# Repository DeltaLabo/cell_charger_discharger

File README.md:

Electrochemical Cell Charger/Discharger/Tester -- README {#mainpage}
============

### Most recent version of this repository can be found in: ###

* [Bitbucket](https://bitbucket.org/juanjorojash/cell_charger_discharger/src/master/)

### Documentation ###

* Full documentation in HTLM version can be found in **[repository directory]/documentation/htlm/index.htlm**

### What is this repository for? ###

* This repository was created to be used in conjuction with the integrated system known as "Charger_discharger.V5". The latest . It was created to control the PIC16F1786 installed for feedback control and serial logging.
* Hardware version: Charger_discharger.V5
* PCB design files  located in **[repository directory]/pcb/**

### How do I get set up? ###

* Connect usign serial cable model "TTL-232R-5V-AJ". 
* **Serial terminal** Start with the following settings BR:57600 kbps, Data: 8 bit, Parity: none, Stop bits: 1, Flow control: none. Press "ESC" to restart and show the main menu. Set the desired configuration following the instructions.
* **LabView logger program** A program for receiving, saving and plotting the test data is included in the repository, in the directory **labview_logger/logger.exe**. The following programs are needed in order to run this program in a PC that **does not** have LabView installed:
	* [LabVIEW Run-Time Engine 2016 - (64-bit)](http://www.ni.com/download/labview-run-time-engine-2016/6067/en/) 
	* [NI-VISA Run-Time Engine 16.0](http://www.ni.com/download/ni-visa-run-time-engine-16.0/6188/en/)
The program creates the directory **c:/logger_data** to store the data.

### Contribution guidelines ###

* If you want to propose a review or need to modify the code for any reason first clone this [repository](https://bitbucket.org/juanjorojash/cell_charger_discharger/src/master/) in your PC and create a new branch for your changes. Once your changes are complete and fully tested ask the administrator permission to push this new branch into the source.
* If you just want to do local changes instead you can download a zip version of the repository and do all changes locally in your PC. 

### Who do I talk to? ###

* [Juan J. Rojas](mailto:juan.rojas@itcr.ac.cr)

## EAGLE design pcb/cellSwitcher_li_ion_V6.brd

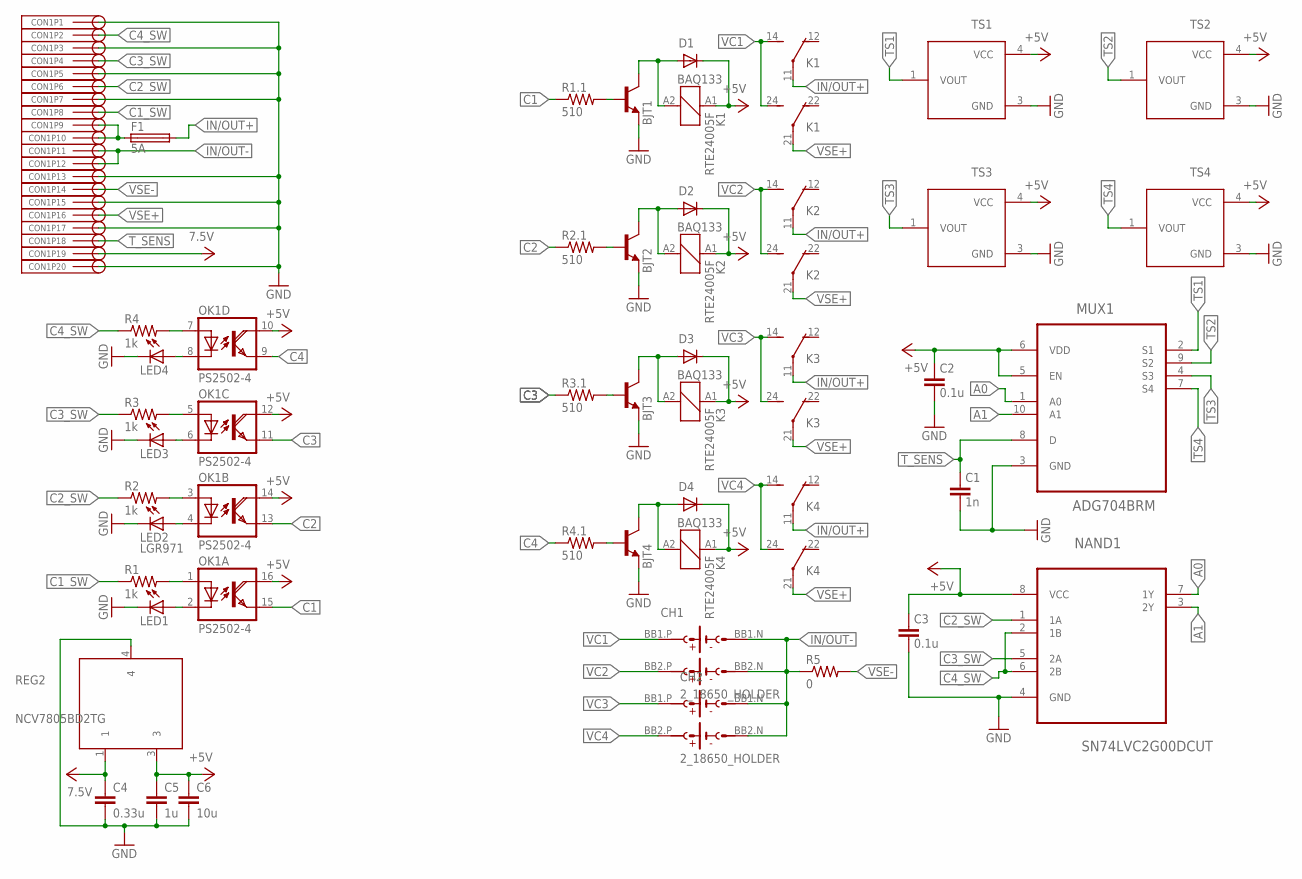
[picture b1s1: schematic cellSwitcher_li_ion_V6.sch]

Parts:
BJT1, BJT2, BJT3, BJT4: BC818K-40; SOT-23
C1: 1n; C0603
C2, C3: 0.1u; C0603
C4: 0.33u; C0603
C5: 1u; C0603
C6: 10u; C0603
CH1, CH2: 2_18650_HOLDER
CON1: TMM-110-01-F-D-RA
D1, D2, D3, D4: BAQ133; SOD08
F1: 5A; SH22,5
K1, K2, K3, K4: RTE24005F
LED1, LED2, LED3, LED4: LGR971; SML0805
MUX1: ADG704BRM; MSOP10
NAND1: SN74LVC2G00DCUT; VSSOP-8
OK1: PS2502-4; DIL16
R1, R2, R3, R4: 1k; R0603
R1.1, R2.1, R3.1, R4.1: 510; R0603
R5: 0; R0603
REG2: NCV7805BD2TG; D2PAK-3
TS1, TS2, TS3, TS4: STLM20DD9F; UDFN-4L

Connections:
7.5V: C4.1, CON1.19, REG2.1
+5V: C2.1, C3.1, C5.1, C6.1, D1.C, D2.C, D3.C, D4.C, K1.A1 (1), K2.A1 (1), K3.A1 (1), K4.A1 (1), MUX1.5 (EN), MUX1.6 (VDD), NAND1.8 (VCC), OK1.10 (COL), OK1.12 (COL), OK1.14 (COL), OK1.16 (COL), REG2.3, TS1.4 (VCC), TS2.4 (VCC), TS3.4 (VCC), TS4.4 (VCC)
A0: MUX1.1 (A0), NAND1.7 (1Y)
A1: MUX1.10 (A1), NAND1.3 (2Y)
C1: OK1.15 (EMI), R1.1.1
C1_SW: CON1.8, R1.1
C2: OK1.13 (EMI), R2.1.1
C2_SW: CON1.6, NAND1.1 (1A), R2.1
C3: OK1.11 (EMI), R3.1.1
C3_SW: CON1.4, NAND1.5 (2A), R3.1
C4: OK1.9 (EMI), R4.1.1
C4_SW: CON1.2, NAND1.2 (1B), NAND1.6 (2B), R4.1
GND: BJT1.2 (E), BJT2.2 (E), BJT3.2 (E), BJT4.2 (E), C1.2, C2.2, C3.2, C4.2, C5.2, C6.2, CON1.1, CON1.3, CON1.5, CON1.7, CON1.13, CON1.15, CON1.17, CON1.20, LED1.C, LED2.C, LED3.C, LED4.C, MUX1.3 (GND), NAND1.4 (GND), REG2.4, TS1.3 (GND), TS2.3 (GND), TS3.3 (GND), TS4.3 (GND)
IN/OUT+: F1.2, K1.11 (COM), K2.11 (COM), K3.11 (COM), K4.11 (COM)
IN/OUT+1: CON1.9, CON1.10, F1.1
IN/OUT-: CH1.BB1.N (B1.N), CH1.BB2.N (B2.N), CH2.BB1.N (B1.N), CH2.BB2.N (B2.N), CON1.11, CON1.12, R5.1
unnamed: BJT1.1 (B), R1.1.2
unnamed: BJT2.1 (B), R2.1.2
unnamed: BJT3.1 (B), R3.1.2
unnamed: BJT3.3 (C), D3.A, K3.A2 (2)
unnamed: LED1.A, OK1.2 (C)
unnamed: LED2.A, OK1.4 (C)
unnamed: LED3.A, OK1.6 (C)
unnamed: LED4.A, OK1.8 (C)
unnamed: OK1.7 (A), R4.2
unnamed: OK1.5 (A), R3.2
unnamed: OK1.3 (A), R2.2
unnamed: OK1.1 (A), R1.2
unnamed: BJT1.3 (C), D1.A, K1.A2 (2)
unnamed: BJT2.3 (C), D2.A, K2.A2 (2)
unnamed: BJT4.1 (B), R4.1.2
unnamed: BJT4.3 (C), D4.A, K4.A2 (2)
TS1: MUX1.2 (S1), TS1.1 (VOUT)
TS2: MUX1.9 (S2), TS2.1 (VOUT)
TS3: MUX1.4 (S3), TS3.1 (VOUT)
TS4: MUX1.7 (S4), TS4.1 (VOUT)
T_SENS: C1.1, CON1.18, MUX1.8 (D)
VC1: CH1.BB1.P (B1.P), K1.14 (NO), K1.24 (NO)
VC2: CH1.BB2.P (B2.P), K2.14 (NO), K2.24 (NO)
VC3: CH2.BB1.P (B1.P), K3.14 (NO), K3.24 (NO)
VC4: CH2.BB2.P (B2.P), K4.14 (NO), K4.24 (NO)
VSE+: CON1.16, K1.21 (COM), K2.21 (COM), K3.21 (COM), K4.21 (COM)
VSE-: CON1.14, R5.2

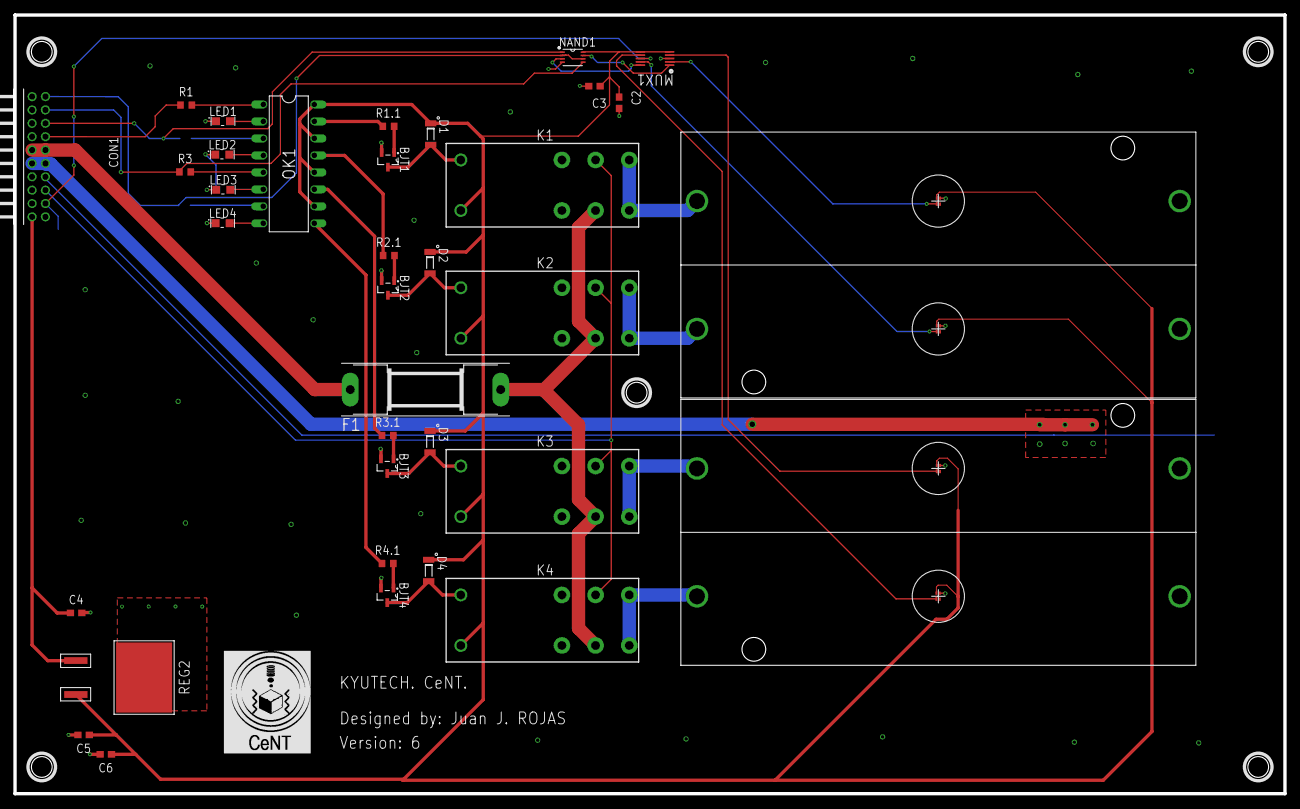
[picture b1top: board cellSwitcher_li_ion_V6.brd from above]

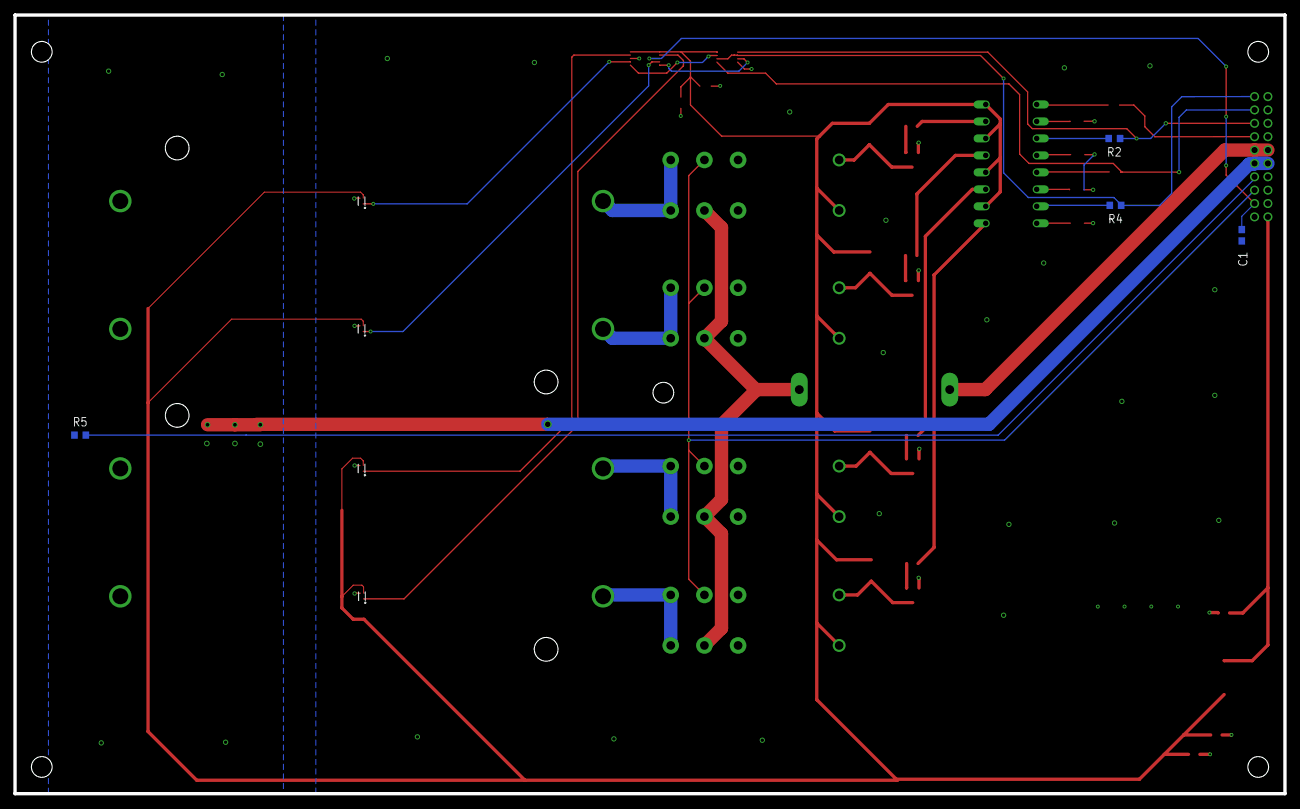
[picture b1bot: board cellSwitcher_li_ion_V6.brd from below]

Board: 2 copper layers, 190.0 x 116.5 mm, 43 parts (4 on the bottom side), 43 nets.

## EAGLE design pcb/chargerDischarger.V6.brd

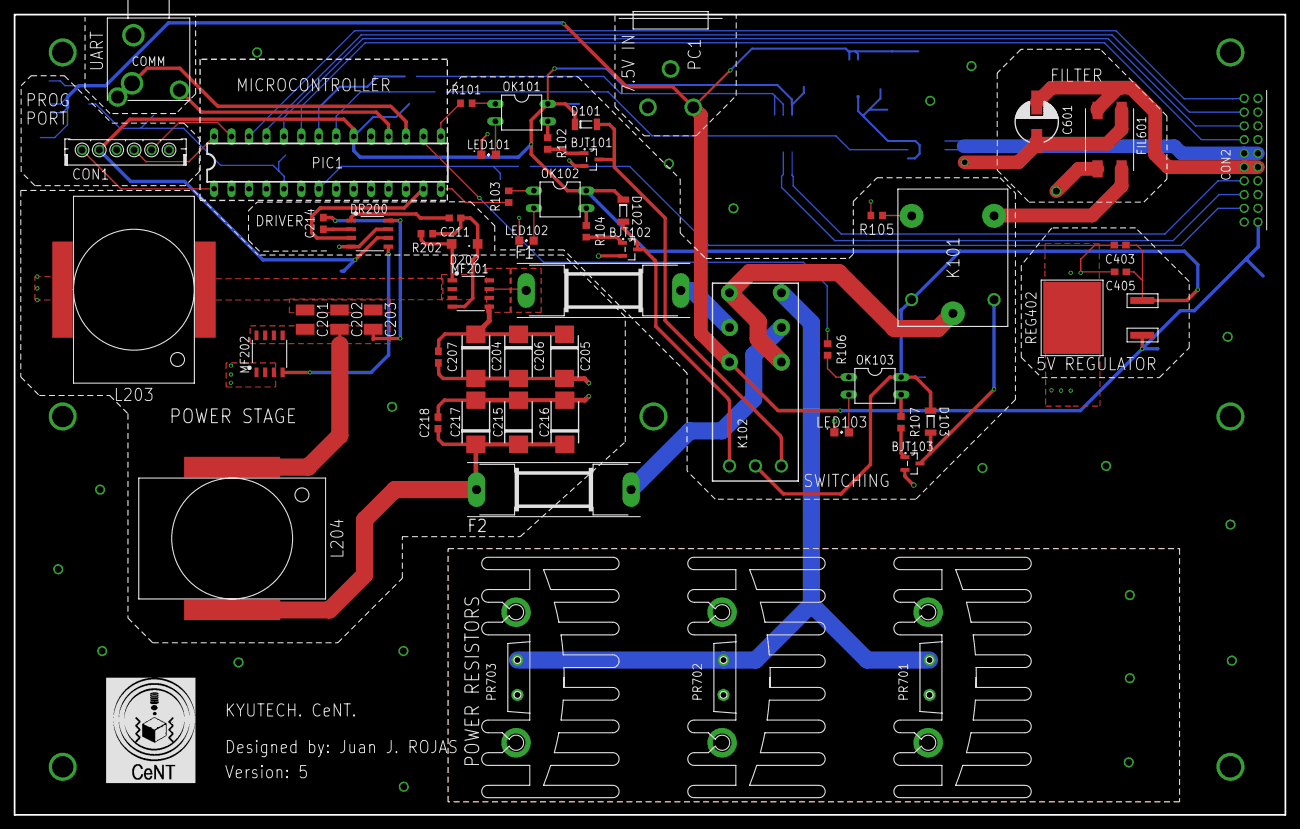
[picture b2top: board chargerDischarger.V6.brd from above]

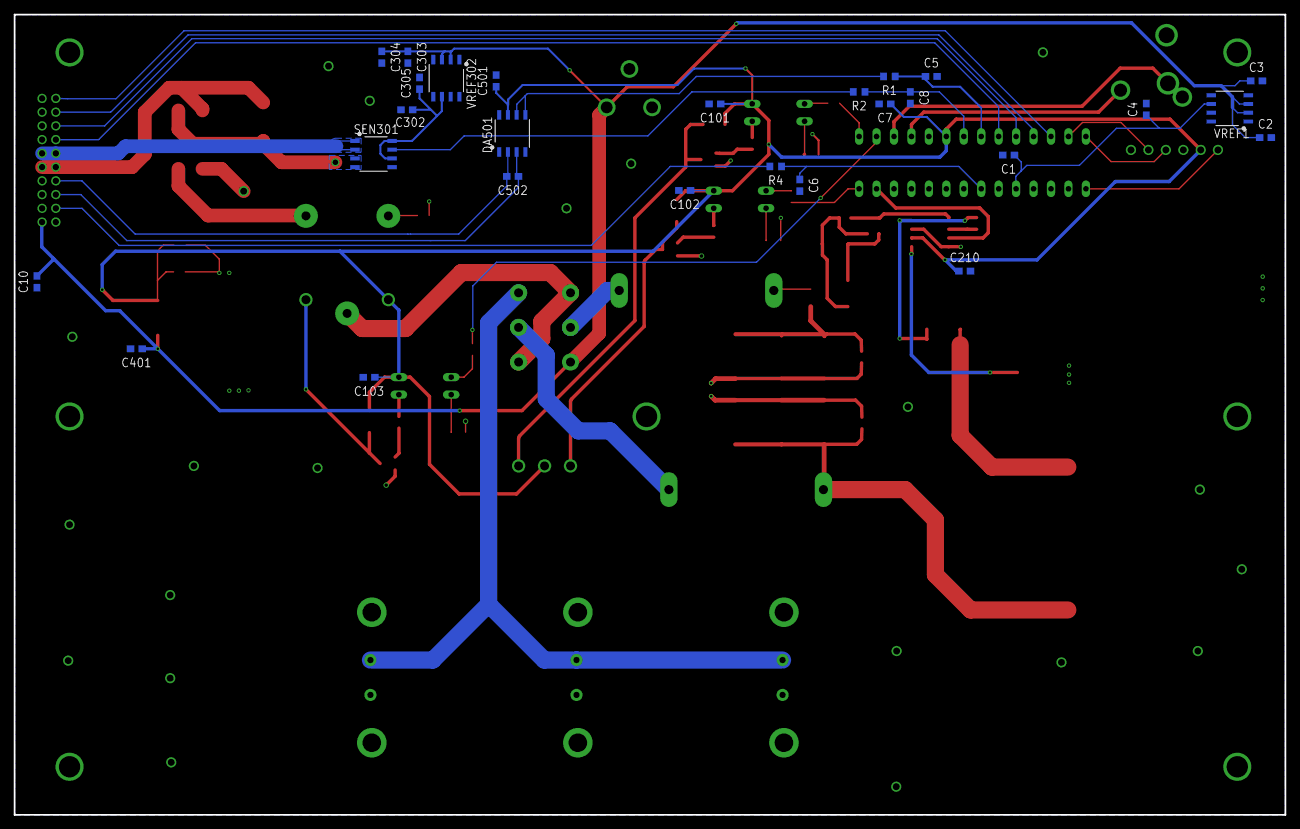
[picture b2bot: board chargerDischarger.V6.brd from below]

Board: 2 copper layers, 185.0 x 116.5 mm, 83 parts (27 on the bottom side), 58 nets.

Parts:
BJT101, BJT102, BJT103: BC818K-40; SOT-23
C1, C3, C6, C7, C101, C102, C103, C210, C214, C302, C304, C403: 1u; C0603
C2, C10, C303, C405: 10u; C0603
C4, C207, C218, C305, C501: 0.1u; C0603
C5, C8, C502: 1n; C0603
C201, C202, C203: 10u; C1210
C204, C205, C206, C215, C216, C217: 33u_Tan; C7343
C211: 10n; C0603
C401: 0.33u; C0603
C601: 100u; D6.3_AEC
COMM: AUDIO_JACK-3.5MM; KLBR4
CON1: B6B-EH-A
CON2: SQT-110-01-F-D-RA
D101, D102, D103: BAQ133; SOD08
D202: SOD123
DA501: MAX4198; SOIC-8
DR200: MCP14628-E/SN; SOIC-8
F1, F2: 4A; SH22,5
FIL601: ACM9070-701
K101: ORWH; ORWH-SS-105D1F
K102: RT424F05054; RT424F05
L203, L204: 68µ; 60B683C
LED101, LED102, LED103: LGR971; SML0805
MF201, MF202: SI4154DY; SOIC-8
OK101, OK102, OK103: PS2502-1; DIL04
PC1: 722RA
PIC1: PIC16F1786-SPDIP; SPDIP-28
PR701, PR702, PR703: 1; TO-220HEATSINK
R1, R2: 0; R0603
R4: 200; R0603
R101, R103, R106, R202: 1k; R0603
R102, R104, R107: 510; R0603
R105: 10M; R0603
REG402: NCV7805BD2TG; D2PAK-3
SEN301: ACS723-05AB-T; SOIC-8
VREF1, VREF302: REF195GSZ; SOIC-8

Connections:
7.5V: C2.1, C3.1, C10.2, C303.1, C304.1, C401.1, CON2.19, K102.22, PC1.PIN, REG402.1, VREF1.2, VREF1.3, VREF302.2, VREF302.3
+5V: C7.1, C101.1, C102.1, C103.1, C210.1, C403.1, C405.1, C501.1, CON1.2, D101.C, D102.C, D103.C, DA501.7, DR200.6, K101.B1, K102.A3, OK101.4, OK102.4, OK103.4, PIC1.20, REG402.3
BI_CURR_MEAS1:N$1: C302.1, C305.1, SEN301.6, SEN301.8, VREF302.6
C1_SW: CON2.8, PIC1.23
C2_SW: CON2.6, PIC1.24
C3_SW: CON2.4, PIC1.25
C4_SW: CON2.2, PIC1.26
CHAR: PIC1.15, R101.1
DISC: PIC1.14, R103.1
GND: BJT101.2, BJT102.2, BJT103.2, C1.2, C2.2, C3.2, C4.2, C5.2, C6.2, C7.2, C8.2, C10.1, C101.2, C102.2, C103.2, C204.-, C205.-, C206.-, C207.2, C210.2, C215.-, C216.-, C217.-, C218.2, C302.2, C303.2, C304.2, C305.2, C401.2, C403.2, C405.2, C501.2, COMM.S, CON1.3, CON2.1, CON2.3, CON2.5, CON2.7, CON2.13, CON2.15, CON2.17, CON2.20, DA501.1, DA501.4, DR200.4, DR200.7, FIL601.P$3, L203.2, LED101.C, LED102.C, LED103.C, MF202.1, MF202.2, MF202.3, PC1.SLEEVE, PC1.SLEEVE_SHUNT, PIC1.8, PIC1.19, PR701.D1, PR701.D2, PR701.R1, PR702.D1, PR702.D2, PR702.R1, PR703.D1, PR703.D2, PR703.R1, R105.2, REG402.4, SEN301.5, VREF1.4, VREF302.4
ICSPCLK: CON1.5, PIC1.27
ICSPDAT: CON1.4, PIC1.28
IN/OUT+: CON2.9, CON2.10, SEN301.1, SEN301.2
IN/OUT-: C601.NEG, CON2.11, CON2.12, FIL601.P$2
I_SENS: R2.2, SEN301.7
MCLR: CON1.1, PIC1.1
unnamed: C8.1, PIC1.21, R2.1
unnamed: C5.1, PIC1.22, R1.1
unnamed: C6.1, PIC1.7, R4.1
unnamed: C1.1, C4.1, PIC1.5, VREF1.6
unnamed: C601.POS, FIL601.P$1, SEN301.3, SEN301.4
unnamed: FIL601.P$4, K101.NO
unnamed: F1.2, K102.21
unnamed: F2.2, K102.11
ON/OFF: PIC1.16, R106.1
POWER_RESISTOR: K102.14, PR701.R2, PR702.R2, PR703.R2
PWM: DR200.3, PIC1.13
RX: COMM.B, COMM.R, PIC1.17
SWITCH1:N$1: BJT101.1, R102.2
SWITCH1:N$2: BJT101.3, D101.A, K102.A1
SWITCH1:N$3: LED102.A, OK102.2
SWITCH1:N$4: OK102.1, R103.2
SWITCH1:N$5: OK102.3, R104.1
SWITCH1:N$6: BJT102.1, R104.2
SWITCH1:N$7: BJT102.3, D102.A, K102.A2
SWITCH1:N$8: K101.NC, R105.1
SWITCH1:N$9: LED103.A, OK103.2
SWITCH1:N$10: OK103.1, R106.2
SWITCH1:N$11: LED101.A, OK101.2
SWITCH1:N$12: OK101.1, R101.2
SWITCH1:N$13: OK101.3, R102.1
SWITCH1:N$14: OK103.3, R107.1
SWITCH1:N$15: BJT103.1, R107.2
SWITCH1:N$16: BJT103.3, D103.A, K101.B2
SWITCH1:TEST: K101.COM, K102.12, K102.24
TX: COMM.T, PIC1.18
T_SENS: CON2.18, R4.2
VSE+: C502.1, CON2.16, DA501.3
VSE-: C502.2, CON2.14, DA501.2
V_SENS: DA501.5, DA501.6, R1.2
ZETA_CONV1:L1_IN1: C201.1, C202.1, C203.1, D202.A, L203.1, MF201.1, MF201.2, MF201.3, R202.2
ZETA_CONV1:L2_IN1: C201.2, C202.2, C203.2, C214.2, DR200.8, L204.1, MF202.5, MF202.6, MF202.7, MF202.8
ZETA_CONV1:N$10: DR200.5, MF202.4
ZETA_CONV1:N$28: C214.1, DR200.2
ZETA_CONV1:N$29: C211.2, DR200.1
ZETA_CONV1:N$30: C211.1, D202.C, MF201.4, R202.1
ZETA_IN: C204.+, C205.+, C206.+, C207.1, F1.1, MF201.5, MF201.6, MF201.7, MF201.8
ZETA_OUT: C215.+, C216.+, C217.+, C218.1, F2.1, L204.2

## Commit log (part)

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2018-07-05 First commit. Configuration bit changed
2018-07-10 Timer0 is working. Some code was included in the main to test that it can count 1 second. WDT needs to be deactivated in order to make this work because they share the same prescaler.
2018-07-10 PWM of 8 bits is ready, out of the oven. Only an 8 bit register to set the DC, from 0 to 100 without change of resolution. The price to pay was changing frequency to 250kHz.
2018-07-10 ADC is working, ready FI BUM DEM. However, the ouput is a little crazy
2018-07-12 Now the measurements of the ADC are correct, the control loop is now at 1kHz. I'm about to make changes to the PID stuff.
2018-07-12 First attemp to make it work in the real stuff.
2018-07-13 Ready for test in the computer usign LabView. Tunning of the controller is not finish and change to switch case is requiered too
2018-07-17 Tested with Labview, test at 200Khz create some sound problems
2018-07-17 Test at 500Khz, same proplem
2018-07-17 125Khz test working, just need to tune everything
2018-07-17 Tune of PI in coarse way, let's see how it reacts
2018-07-17 At 125Khz everything works fine, however incorporating the Differential part of the controller seems now a good idea. I could really improve the CV part.
2018-07-19 Many changes, see if I can make it work
2018-07-20 A problem with the transition between CC and CV, I will solve it. The rest is better than anytime before
2018-08-01 Some incremental stepping in the ki when CV is reached. Also right now is running with FCCM of the mosfet driving chip activated.
2018-08-01 This is the real working point!!
2018-08-01 Very good behaviour at low current. Incremental of the duty cycle can be a good idea.
2018-08-03 Some changes to the way it logs in TESTBENCH
2018-08-03 Implemented STANDBY and IDLE state
2018-08-03 CHARGE DISCHARGE AND PRECHARGE IMPLEMENTED
2018-08-03 DC res calculations implemented as switch and function
2018-08-03 WAIT state is implemented, PARAmeters are set with converter_setting fucntions
2018-08-03 Fixed WAIT implementation
2018-08-03 Implemented both ISDONE and FAULT
2018-08-03 All Parameter definition for LI-Ion changed to switch-case
2018-08-03 Move the timing outside the log function
2018-08-03 Forgot to stage the Main.c in previous commit
2018-08-03 Error of charging after discharge is not solved, but still is quite good.
2018-08-03 Error was reduce to 200 is a big change so better take a look at it again
2018-08-04 The error was fixed adding capacitors to the output of the regulator and the branches.
2018-08-05 Timing is changed to use 2ms period and the results are not so good, for some reason the constants are not working anymore,
2018-08-06 Just testing, the timing was increased to 4 ms per cycle, but still gives error, there is something very slow....
2018-08-06 I made many changes, and was able to solve the things about timing errors, unfortunately that leads to a period of 4 ms between control cycles, which is not good.
2018-08-07 First version of documentation using Doxygen, also several changes in char literals.
2018-08-07 Before implementation of GOTO in the parameter stuff
2018-08-08 Change to floats, and goto was added, stop and restart the UART interruptions
2018-08-08 Very stable version.
2018-08-08 Just set the voltage offset for this particular case
2018-08-09 Everything is now change to float, but comments were lost in the way
2018-08-09 Start_state_machine and Define_param are fully documented now
2018-08-09 Include Define_param in fSTANDBY
2018-08-09 Initial version of README and other changes
2018-08-10 Documentation of several files, most of the changes in the state machine.c
2018-08-11 Fixed the state machine, by changing the variable previous_state to prev_or_next_state
2018-08-11 More documentation, I just found an error in the state machine, after the wating it does not come back to the usual operation
2018-08-11 Reverse the change in prev_state, to much change led to failure...
2018-08-29 Include temperature measurements, Choke filter was install, and worked perfect
2018-08-30 First version of Ni-MH, the resistor need to be reduced to 1ohm or something like that
2018-08-30 Timming to do control every 2ms and 500 count.
2018-08-30 Timing is directly set to 4ms with timer 0. Log works ok now
2018-08-31 Capacity now works OK, there was a timing problem when using ltoa, so i decided to use utoa instead, so now maximum capacity that can be recorded is 0xFFFF
2018-09-01 Inlcude a termination for the log, and reset the capacity buffer
2018-09-02 Several change. Serial interrupt was changed to avoid interference with the STANDBY state. Header guard in hardware.h. Change of waiting string to W[0-9]+W. Include timeout for charging
2018-09-02 Change capacity of Ni_MH to 2000. Include small changes in documentation
2018-09-02 Change PRECHARGE to PRE and now is always a DISCHARGE process. Many changes, need to evaluate
2018-09-06 Two new states were added. POSTCHARGE and PS_DC_res. Also the PRECHARGE was changed to PREDISCHARGED and all the state machine as reconfigured accordingly. Now the option menu is the same for both ch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
2018-09-07 Include temperature instead of duty cycle. Incude Cell number and state number in waiting and DC_res states log
2018-09-07 It seems there is a problem still with the PS_DC_res but I don't know where it comes from, testing again to see. Changed the way the states are sent in the log, because it was bad, it only worked for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
2018-09-09 Only one function to define parameters of both chemistries
2018-09-09 Eliminate the parameter setting for Li_ion, now is unified
2018-09-13 Include 0.8 max DC.
2018-09-19 Fully documented main.c, there are somo changes in the main loop that require testing
2018-09-19 Clear the code in the interruption for the main.c
2018-09-22 Include LabView logger in the repository
2018-09-22 Change directory and include app file
2018-09-22 Several changes in documentation. state_machine.h fully documented, changes in README.
2018-09-24 Counter for end of charge and end of discharge were eliminated. A lot of documentation was added. Now still in hardware.c
2018-09-24 Documentation of hardware.c finished.
2018-09-24 More documentation, nothing special. Add CC_kp and CC_ki
2018-09-25 First version for testinf Li-PO. With a HACK
2018-09-27 More documentation, now switching to new program
2018-09-27 More documentation
2018-09-27 Initial approach to the new board, not tested yet
2018-09-28 To work with LIPO the CV_kp was changed from 0.4 to 0.2 and the CV_ki was changed from 0.5 to 0.4. Also there was an error in the fCHARGE, should be implemented in the other program
2018-10-01 Change in the logging, errror in minutes after 99 was solved
2018-10-12 Working perfect! Taking out all the bias in the ADC, got to recalibrate! SET_CHAR and SET_DISC were backwards. And STOP_CONVERTER() also. I removed the HACKS for the previous board.
2018-10-14 The outputs for the cells were fixed. Some issue with settling time, it was too fast. Voltage measurement was corrected, now there is no voltage divider. The average of the values is now done with CO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
2018-10-16 New Labview executable program
2019-02-21 Increase DC max to 0.8 it was to low so it gave problems when there is too much voltage drop. I change the main so it always check the CV value.
2019-06-30 All the changes made in the Birds3 PC
2019-07-01 First try, unsuccessful
2019-07-02 Some changes but not tested yet
2019-07-02 Not tested changes
2019-07-03 Include .vscode in gitnore and make several change that almost let it run good. It shows a warning of High temperature
2019-07-04 Almost done. The charge is working but discharge is under test. For cancelling the process now is neccessary to press "c" instead of ESC. This is because the arrows are detected as ESC for some reaso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
2019-07-04 Reduce the size of the program by taking the buffers out
2019-07-04 Logger was out of the screen
2019-07-05 Problem with the current value
2019-07-05 Time for a real tune of the constants
2019-07-07 Only the resistance part is peding
2019-07-07 New way to get the resistance
2019-07-10 Solved the two errors
2019-07-10 Solve the problem of printing by usign utoa again, solve the problem of vmax by putting it as part of the log.
2019-07-13 Taken from the BIRDS3 PC
2019-07-14 Changes in documentation
2019-07-26 WPUE3 is activated
2020-10-28 new board versions
2021-01-23 Create LICENSE
2023-02-06 first day in the lab
2023-02-17 from bitbucket
2023-02-21 PCB_PDFs
    This contains the schematics and boards of the charger/discharger
2023-12-12 new command manual
2023-12-20 new serial interface initial commit
2023-12-21 problem with little endian
2023-12-21 checksum is not working
2023-12-21 all commands working
2023-12-21 eliminate strings and functions
2023-12-21 log_data ready
2023-12-21 added some of the old stuff
2023-12-22 working_version
    new constant current for charge and discharge
2024-02-15 Next State and Next Cell
    The bottons of Next State and Next Cell are all ready working as intended. A state_machine_b.c file is created for testing future changes.
2024-02-20 State machine back on
    The state machine function is back on and the functions of next state, next cell and next repetition are refined.
2024-02-22 Charge baterry functioning
    Changes for the charge function to work have been made
2024-03-01 Progress on implementing discharge
    Friday first of march. Advanced in implementing discharge and changes of the reset and idel state.
2024-03-06 Update2 basic_configuration_struct changes_kyutech_2023.md
2024-03-19 cambios de pid y algo de estados
    todavia peta de vez en cuando
2024-04-18 <converter configuration and interrupt work
    converter configuration is now functional, further testing is needed.
    a function called interrupt enable was done for trying to solve next state and next cell errors
    cargue variable is now a float and is seem to be working well, further testing is needed
2024-04-19 Test results directory
    In this directory, csvs with the data gather form test are going to be uploaded for its future plot
2024-04-22 NMH-testing
2024-04-26 commit 26/4/24
2024-05-06 new build
2024-05-16 Next State, Next cell and Next Repetition Solved
    This patch solve the interruption problem that didnt let the nextState, nextRepetition and nextCell work the way it was intended.
    Future patches will be focus on cleanin the code, properly commented and quality of life updates such as the implementation of default values for bothe NMH and LI k values for the pid.
2024-08-19 Revision on next state failure
    Se ponen algunas constantes y se quitan los #if y #else para que funcione con cualquier batería. Se trabaja en la detección de errores de comunicación
2024-08-29 Next state fixed
    Changes on the definition of the messages for next state, next cell and reset. Change in how the interruption of UART is being managed.
2024-08-29 wait time between repetitons corrected
2024-09-02 Documentation on frame changes
    Changes on converting settings and action commands
2024-09-02 Removal of unnecesary functions
    The functions that are not beeing used were eliminated for optimization.
2024-09-02 Removal of unnecessary variables
2024-09-19 Advances on a python interface for testing and calibration
    Advances on a python interface for testing and calibration
2024-10-16 new app
2025-02-05 Delete Test_Result/Charge2.csv
    Deleted old test results
2025-02-05 Delete Test_Result/DC Resistance_17_05_24_15_07_55.csv
    Deleted old test results
2025-02-05 Delete Test_Result/DC Resistance_17_05_24_16_44_24.csv
    Deleted old test results
2025-02-05 Delete Test_Result/Discharge3.csv
    Deleted old test results
2025-02-05 Delete Test_Result/Slow_Discharge.csv
    Deleted old test results
2025-02-05 Upload test results from 05-02-2025 at Costa Rica
2025-02-13 DC resistance patch
2025-02-13 test results for li-ion
2025-02-13 Test Li-ion data
2025-02-17 folders and files working properly
2025-02-20 Python Calibration Programm Added
2025-02-27 New DC_Resistance test implemented based on IEC 61960-3
    Changed the test for DC-Resistance to one based on IEC 61960-3. Also, added a dc_res post processing file.
2025-02-27 Fixed headers on script
